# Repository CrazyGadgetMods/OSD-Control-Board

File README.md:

# OSD Control Board
This OSD board is a simple set of logic gates that allow the screen driver boards used in portables to be controlled with button combinations from the built-in controller. This was a first-rev board *very* early venture into PCB design, so it could definitely use some tweaks like decoupling caps for the logic gates, and the use of a proper ground plane. The board works fine as-is, or you could integrate it into your own design!

## Using the Board
LT, RT, Z and S held together trigger the master key which, in combination with the following buttons will trigger the outputs wired to the screen driver board:
- DU: +
- DD: -
- DL: Source
- DR: Menu

Keep in mind, you can change the master button combination (or any of the other buttons) to better fit to your portable. For example, I like to wire S on the OSD board to Z2 on my GC+ in all my Ashidas, as the original button combination was not ergonomic. Likewise, you can tie multiple inputs together if you want a master combo with less buttons.

## Credits
- [BitBuilt](https://bitbuilt.net/): Being the best modding community out there!
- [Gman](https://github.com/Gmanmodz): Sanity checking

## License
Solderpad Hardware License v2.1

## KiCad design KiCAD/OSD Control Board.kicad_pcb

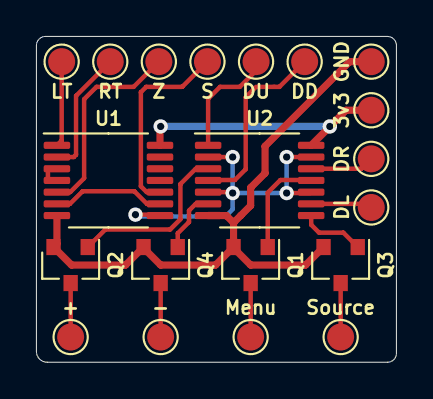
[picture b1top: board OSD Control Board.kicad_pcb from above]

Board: 2 copper layers, 20.0 x 18.1 mm, 20 parts (0 on the bottom side), 21 nets.

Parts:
3v3: 3v3; TestPoint_Pad_D1.5mm
+: +; TestPoint_Pad_D1.5mm
-: -; TestPoint_Pad_D1.5mm
DD: DD; TestPoint_Pad_D1.5mm
DL: DL; TestPoint_Pad_D1.5mm
DR: DR; TestPoint_Pad_D1.5mm
DU: DU; TestPoint_Pad_D1.5mm
GND: GND; TestPoint_Pad_D1.5mm
LT: LT; TestPoint_Pad_D1.5mm
Menu: Menu; TestPoint_Pad_D1.5mm
Q1, Q2, Q3, Q4: NX138AKR; SOT-23
RT: RT; TestPoint_Pad_D1.5mm
S: S; TestPoint_Pad_D1.5mm
Source: Source; TestPoint_Pad_D1.5mm
U1: SN74HCS32PWR; TSSOP-14_4.4x5mm_P0.65mm
U2: SN74HCS7002PWR; TSSOP-14_4.4x5mm_P0.65mm
Z: Z; TestPoint_Pad_D1.5mm

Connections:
+3V3: 3v3.1, U1.14, U2.14
/2A: U1.3, U1.4
/3A: U1.6, U1.9
/+N: Q2.1, U2.3
/-N: Q4.1, U2.6
/DD: DD.1, U2.4
/DL: DL.1, U2.9
/DR: DR.1, U2.12
/DU: DU.1, U2.1
/LT: LT.1, U1.1
/MenuN: Q1.1, U2.11
/OR_OUT: U1.8, U2.2, U2.5, U2.10, U2.13
/RT: RT.1, U1.2
/S: S.1, U1.10
/SourceN: Q3.1, U2.8
/Z: U1.5, Z.1
GND: GND.1, Q1.2, Q2.2, Q3.2, Q4.2, U1.7, U2.7
unnamed: Menu.1, Q1.3
unnamed: +.1, Q2.3
unnamed: Q3.3, Source.1
unnamed: -.1, Q4.3

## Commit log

2024-05-08 init
